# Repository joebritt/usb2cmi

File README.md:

# usb2cmi
USB Keyboard &amp; Mouse interface for the Fairlight CMI

More info can be found here:

https://docs.google.com/document/d/1SBbrsyc7bVfPzIFhJmcOLwGjMr6u-KO0Lp5tNpQLhYE/edit?usp=sharing

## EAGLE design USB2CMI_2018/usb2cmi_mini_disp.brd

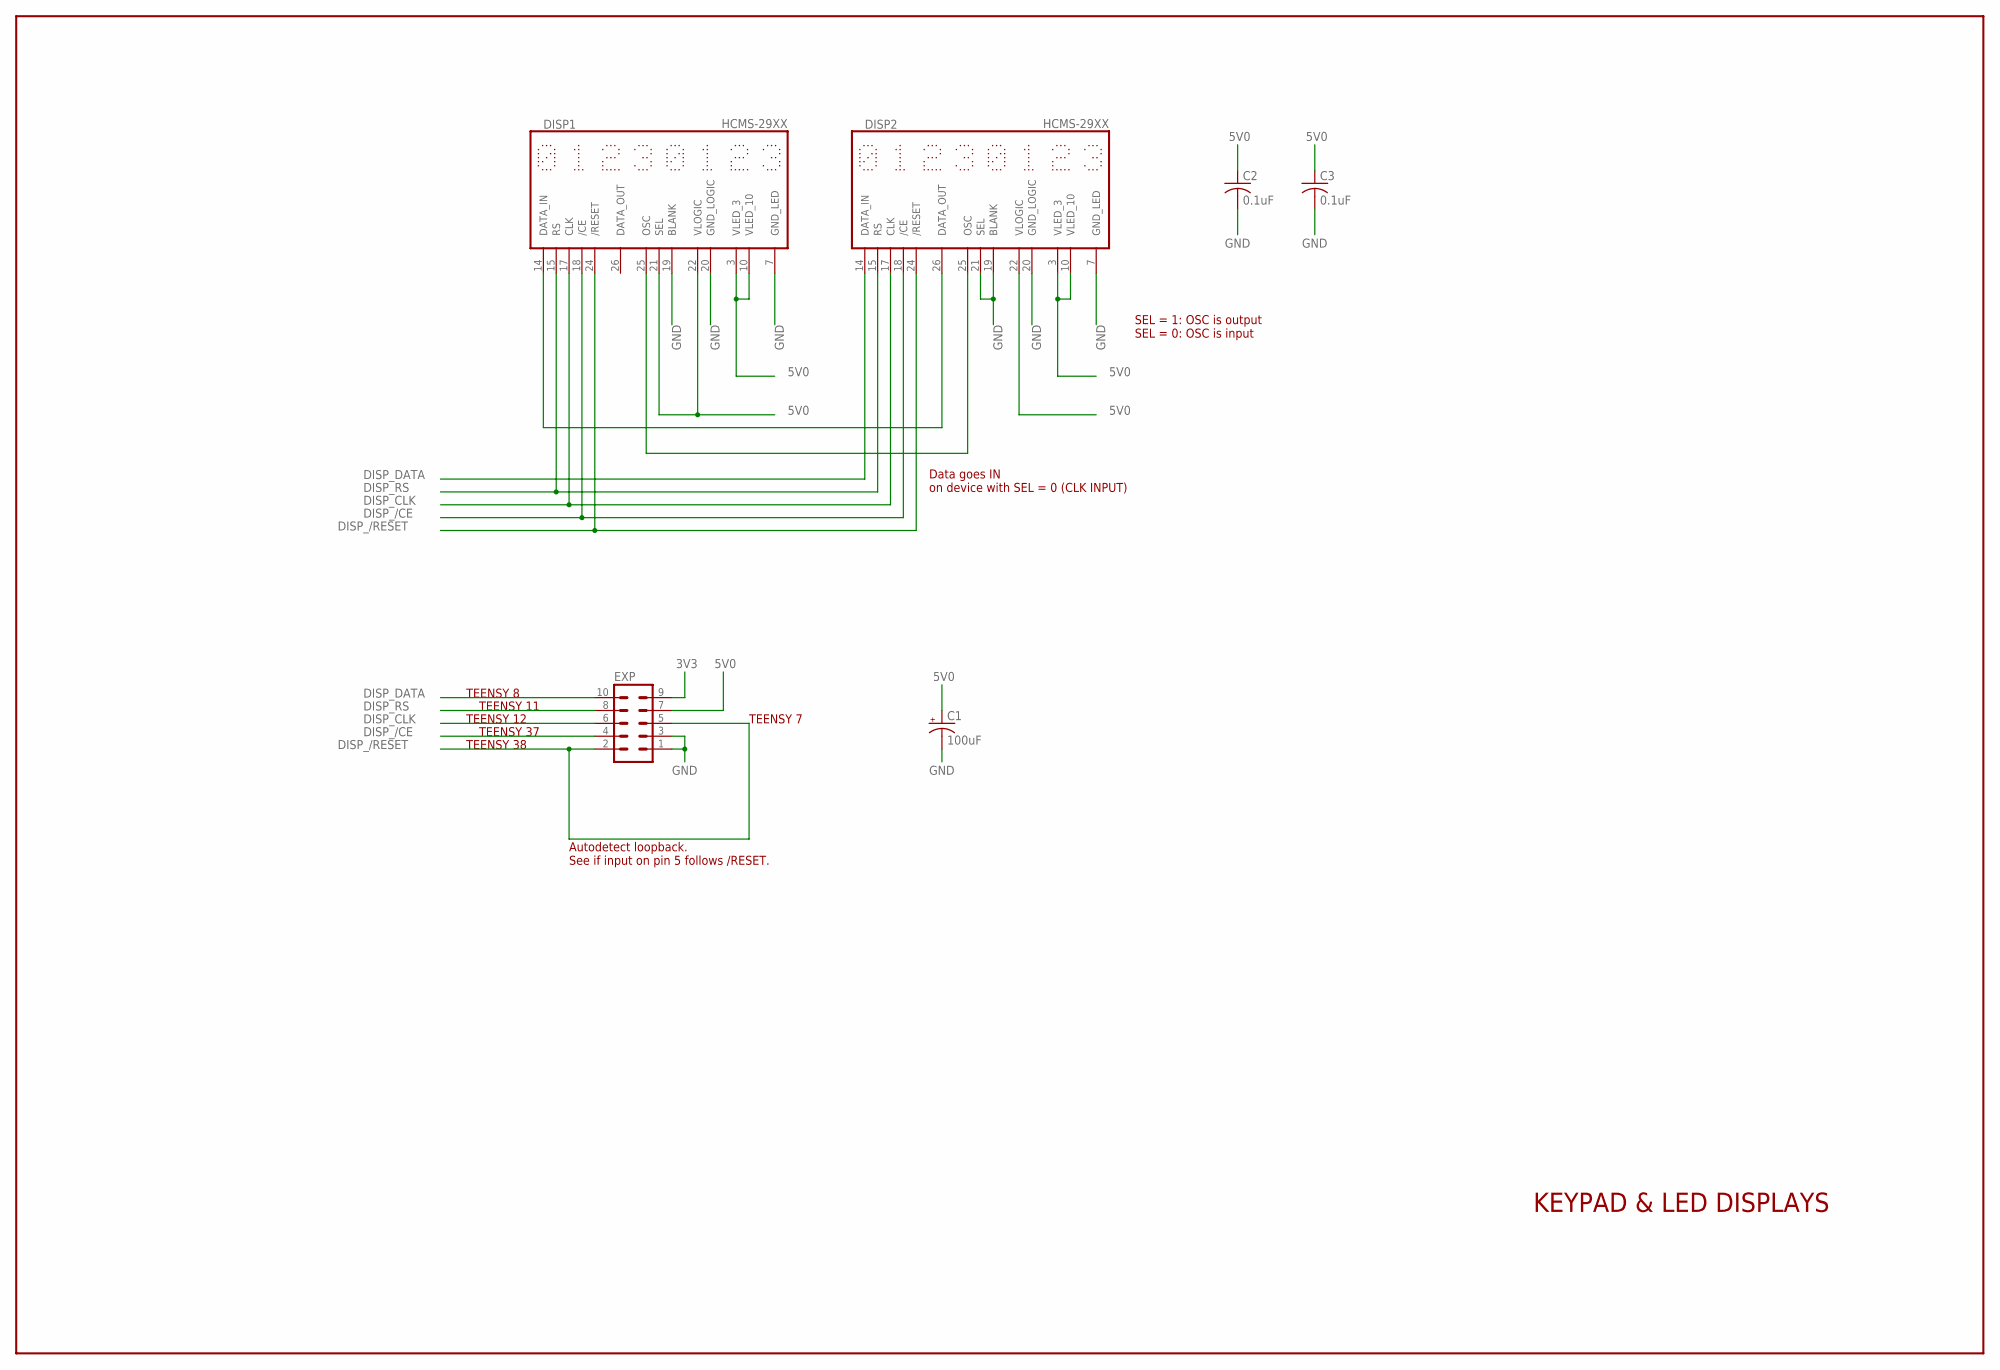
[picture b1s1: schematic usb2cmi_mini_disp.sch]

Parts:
C1: 100uF; E2,5-7
C2, C3: 0.1uF; C050-025X075
DISP1, DISP2: HCMS-29XX
EXP: MA05-2

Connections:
3V3: EXP.9
5V0: C1.+, C2.1, C3.1, DISP1.3 (VLED_3), DISP1.10 (VLED_10), DISP1.21 (SEL), DISP1.22 (VLOGIC), DISP2.3 (VLED_3), DISP2.10 (VLED_10), DISP2.22 (VLOGIC), EXP.7
DISP_/CE: DISP1.18 (/CE), DISP2.18 (/CE), EXP.4
DISP_/RESET: DISP1.24 (/RESET), DISP2.24 (/RESET), EXP.2, EXP.5
DISP_CLK: DISP1.17 (CLK), DISP2.17 (CLK), EXP.6
DISP_DATA: DISP2.14 (DATA_IN), EXP.10
DISP_RS: DISP1.15 (RS), DISP2.15 (RS), EXP.8
GND: C1.-, C2.2, C3.2, DISP1.7 (GND_LED), DISP1.19 (BLANK), DISP1.20 (GND_LOGIC), DISP2.7 (GND_LED), DISP2.19 (BLANK), DISP2.20 (GND_LOGIC), DISP2.21 (SEL), EXP.1, EXP.3
unnamed: DISP1.14 (DATA_IN), DISP2.26 (DATA_OUT)
unnamed: DISP1.25 (OSC), DISP2.25 (OSC)

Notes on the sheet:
KEYPAD & LED DISPLAYS
SEL = 1: OSC is output SEL = 0: OSC is input
Autodetect loopback. See if input on pin 5 follows /RESET.
Data goes IN on device with SEL = 0 (CLK INPUT)
TEENSY 7
TEENSY 38
TEENSY 37
TEENSY 12
TEENSY 11
TEENSY 8

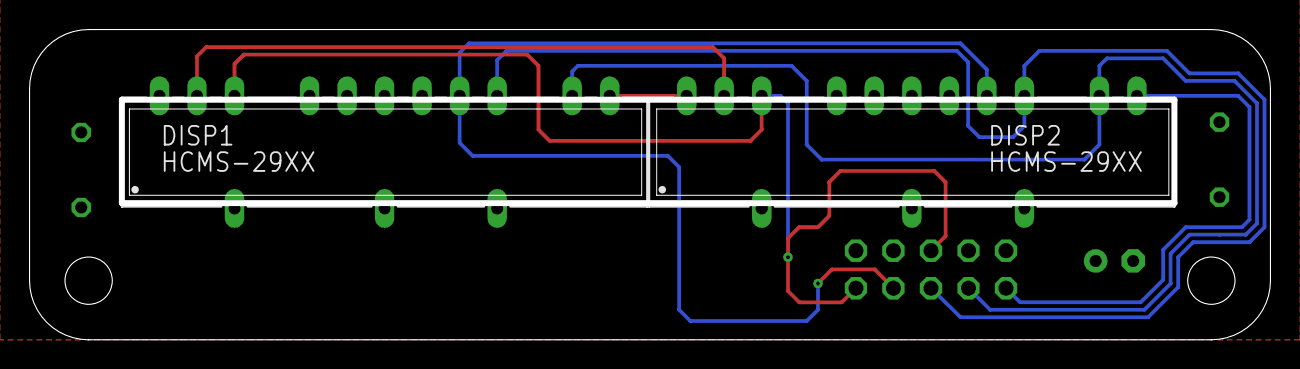
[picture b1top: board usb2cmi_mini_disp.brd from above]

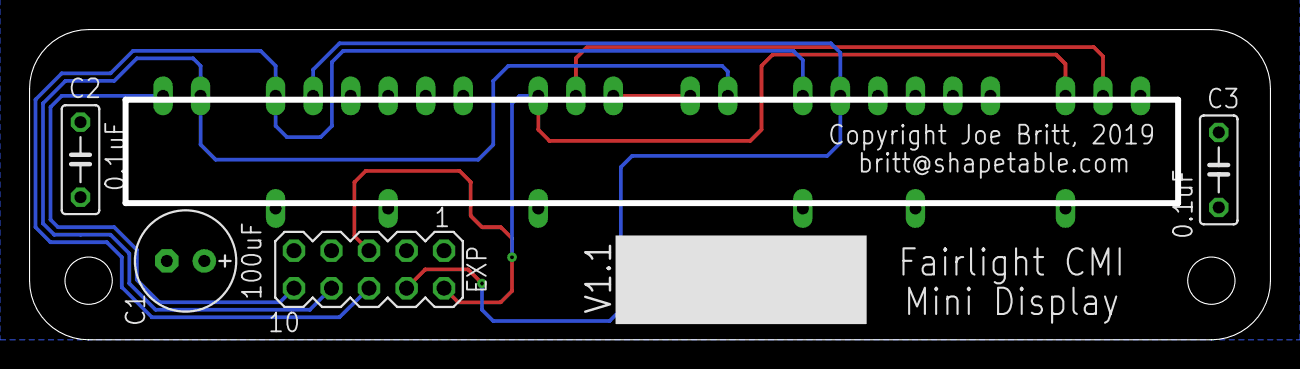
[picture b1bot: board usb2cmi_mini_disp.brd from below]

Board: 2 copper layers, 84.0 x 21.0 mm, 6 parts (4 on the bottom side), 9 nets.

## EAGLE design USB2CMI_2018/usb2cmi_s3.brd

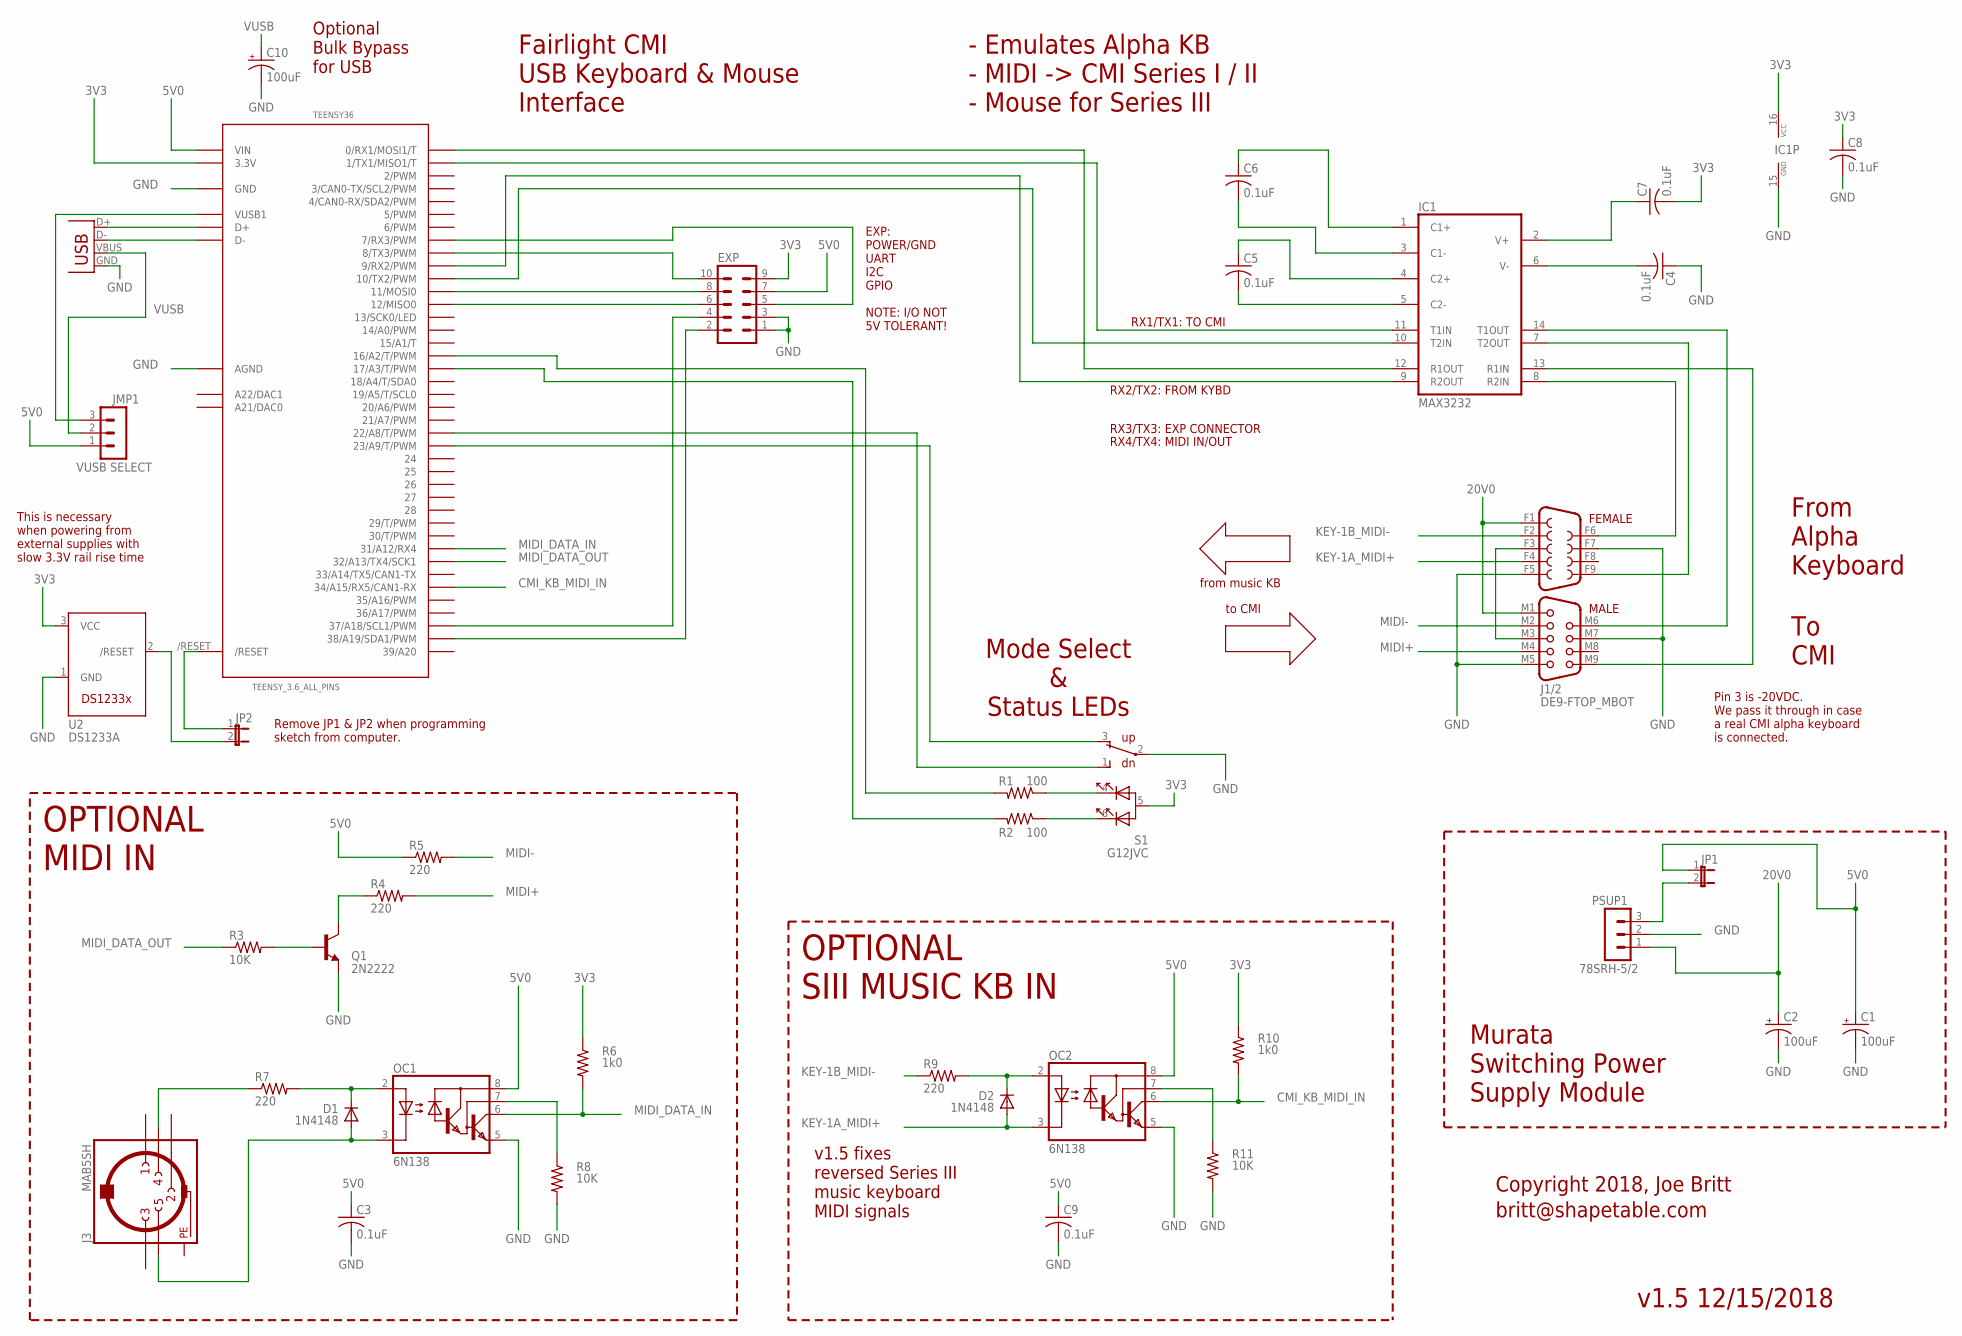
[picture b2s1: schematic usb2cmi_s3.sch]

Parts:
C1, C10: 100uF; E2,5-7
C2: 100uF; E3,5-10
C3, C4, C5, C6, C7, C8, C9: 0.1uF; C050-025X075
D1, D2: 1N4148; DO35-7
EXP: MA05-2
IC1: MAX3232; DIL16
J1/2: DE9-FTOP_MBOT; DE9_FTOP_MBOT
J3: MAB5SH
J4: USB-A-H
JMP1: VUSB SELECT; MA03-1
JP1, JP2: JP1E; JP1
OC1, OC2: 6N138; DIL08-NARROW
PSUP1: 78SRH-5/2; MA03-1
Q1: 2N2222; TO92-EBC-OVAL
R1, R2: 100; 0207/10
R3, R8, R11: 10K; 0207/10
R4, R5, R7, R9: 220; 0207/10
R6, R10: 1k0; 0207/10
S1: G12JVC
TEENSY36: TEENSY_3.6_ALL_PINS
U2: DS1233A; TO-92-

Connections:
3V3: C7.2, C8.1, EXP.9, IC1.16 (VCC), R6.1, R10.1, S1.5 (A), TEENSY36.3.3V, TEENSY36.3.3V3 (3.3V), U2.3 (VCC)
5V0: C1.+, C3.1, C9.1, EXP.7, JMP1.1, JP1.1, OC1.8 (VCC), OC2.8 (VCC), R5.1, TEENSY36.VIN
20V0: C2.+, J1/2.F1, J1/2.M1, PSUP1.1
CMI_KB_MIDI_IN: OC2.6 (VO), R10.2, TEENSY36.34/A15 (34/A15/RX5/CAN1-RX)
GND: C1.-, C2.-, C3.2, C4.1, C8.2, C9.2, C10.-, EXP.1, EXP.3, IC1.15 (GND), J1/2.F5, J1/2.F7, J1/2.M5, J1/2.M7, J4.GND, OC1.5 (GND), OC2.5 (GND), PSUP1.2, Q1.E, R8.2, R11.2, S1.2 (COM), TEENSY36.AGND, TEENSY36.GND, TEENSY36.GND1 (GND), TEENSY36.GND3 (GND), TEENSY36.GND4 (GND), U2.1 (GND)
KEY-1A_MIDI+: D2.A, J1/2.F4, OC2.3 (C)
KEY-1B_MIDI-: J1/2.F2, R9.1
MIDI+: J1/2.M4, R4.2
MIDI-: J1/2.M2, R5.2
MIDI_DATA_IN: OC1.6 (VO), R6.2, TEENSY36.31/A12 (31/A12/RX4)
MIDI_DATA_OUT: R3.1, TEENSY36.32/A13 (32/A13/TX4/SCK1)
unnamed: JP2.1, TEENSY36./RESET
unnamed: JP2.2, U2.2 (/RESET)
unnamed: EXP.5, TEENSY36.7 (7/RX3/PWM)
unnamed: EXP.10, TEENSY36.8 (8/TX3/PWM)
unnamed: EXP.8, TEENSY36.11 (11/MOSI0)
unnamed: EXP.6, TEENSY36.12 (12/MISO0)
unnamed: IC1.9 (R2OUT), TEENSY36.9 (9/RX2/PWM)
unnamed: R1.1, S1.4 (K_RED)
unnamed: R2.1, S1.6 (K_GRN)
unnamed: R2.2, TEENSY36.17/A3 (17/A3/T/PWM)
unnamed: R1.2, TEENSY36.16/A2 (16/A2/T/PWM)
unnamed: S1.1 (DOWN), TEENSY36.22/A8 (22/A8/T/PWM)
unnamed: S1.3 (UP), TEENSY36.23/A9 (23/A9/T/PWM)
unnamed: J4.D+, TEENSY36.D+
unnamed: J4.D-, TEENSY36.D-
unnamed: JMP1.3, TEENSY36.VUSB1
unnamed: C5.2, IC1.5 (C2-)
unnamed: C5.1, IC1.4 (C2+)
unnamed: C6.2, IC1.3 (C1-)
unnamed: C6.1, IC1.1 (C1+)
unnamed: C4.2, IC1.6 (V-)
unnamed: IC1.11 (T1IN), TEENSY36.1 (1/TX1/MISO1/T)
unnamed: Q1.B, R3.2
unnamed: IC1.14 (T1OUT), J1/2.M6
unnamed: C7.1, IC1.2 (V+)
unnamed: D1.C, OC1.2 (A), R7.2
unnamed: D1.A, J3.5, OC1.3 (C)
unnamed: Q1.C, R4.1
unnamed: J3.4, R7.1
unnamed: IC1.13 (R1IN), J1/2.M9
unnamed: IC1.12 (R1OUT), TEENSY36.0 (0/RX1/MOSI1/T)
unnamed: IC1.10 (T2IN), TEENSY36.10 (10/TX2/PWM)
unnamed: IC1.8 (R2IN), J1/2.F6
unnamed: IC1.7 (T2OUT), J1/2.F9
unnamed: J1/2.F3, J1/2.M3
unnamed: OC1.7 (VB), R8.1
unnamed: JP1.2, PSUP1.3
unnamed: D2.C, OC2.2 (A), R9.2
unnamed: OC2.7 (VB), R11.1
PE: J3.PE, J3.PE@ (PE)
SCL1: EXP.4, TEENSY36.37/A18 (37/A18/SCL1/PWM)
SDA1: EXP.2, TEENSY36.38/A19 (38/A19/SDA1/PWM)
VUSB: C10.+, J4.VBUS, JMP1.2

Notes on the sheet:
OPTIONAL MIDI IN
Murata Switching Power Supply Module
From Alpha Keyboard
To CMI
RX1/TX1: TO CMI
RX2/TX2: FROM KYBD
RX3/TX3: EXP CONNECTOR
RX4/TX4: MIDI IN/OUT
EXP: POWER/GND UART I2C GPIO NOTE: I/O NOT 5V TOLERANT!
Mode Select & Status LEDs
Pin 3 is -20VDC. We pass it through in case a real CMI alpha keyboard is connected.
Copyright 2018, Joe Britt
britt@shapetable.com
Fairlight CMI USB Keyboard & Mouse Interface
- Emulates Alpha KB - MIDI -> CMI Series I / II - Mouse for Series III
This is necessary when powering from external supplies with slow 3.3V rail rise time
Remove JP1 & JP2 when programming sketch from computer.
from music KB
to CMI
OPTIONAL SIII MUSIC KB IN
Optional Bulk Bypass for USB
v1.5 fixes reversed Series III music keyboard MIDI signals
v1.5 12/15/2018

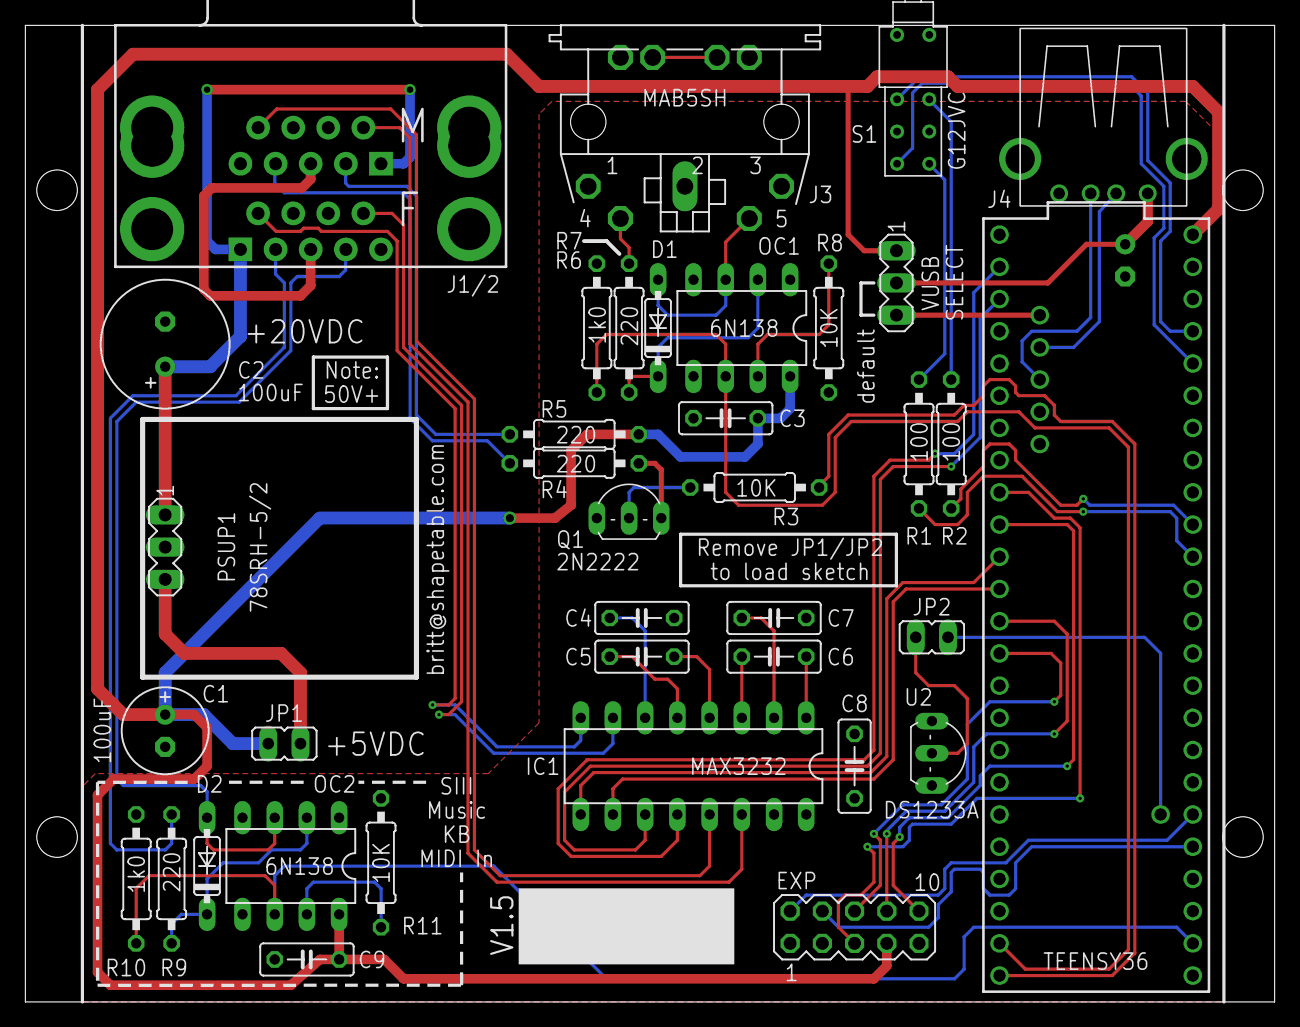
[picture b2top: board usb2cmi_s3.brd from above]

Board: 2 copper layers, 98.5 x 77.0 mm, 38 parts (1 on the bottom side), 54 nets.

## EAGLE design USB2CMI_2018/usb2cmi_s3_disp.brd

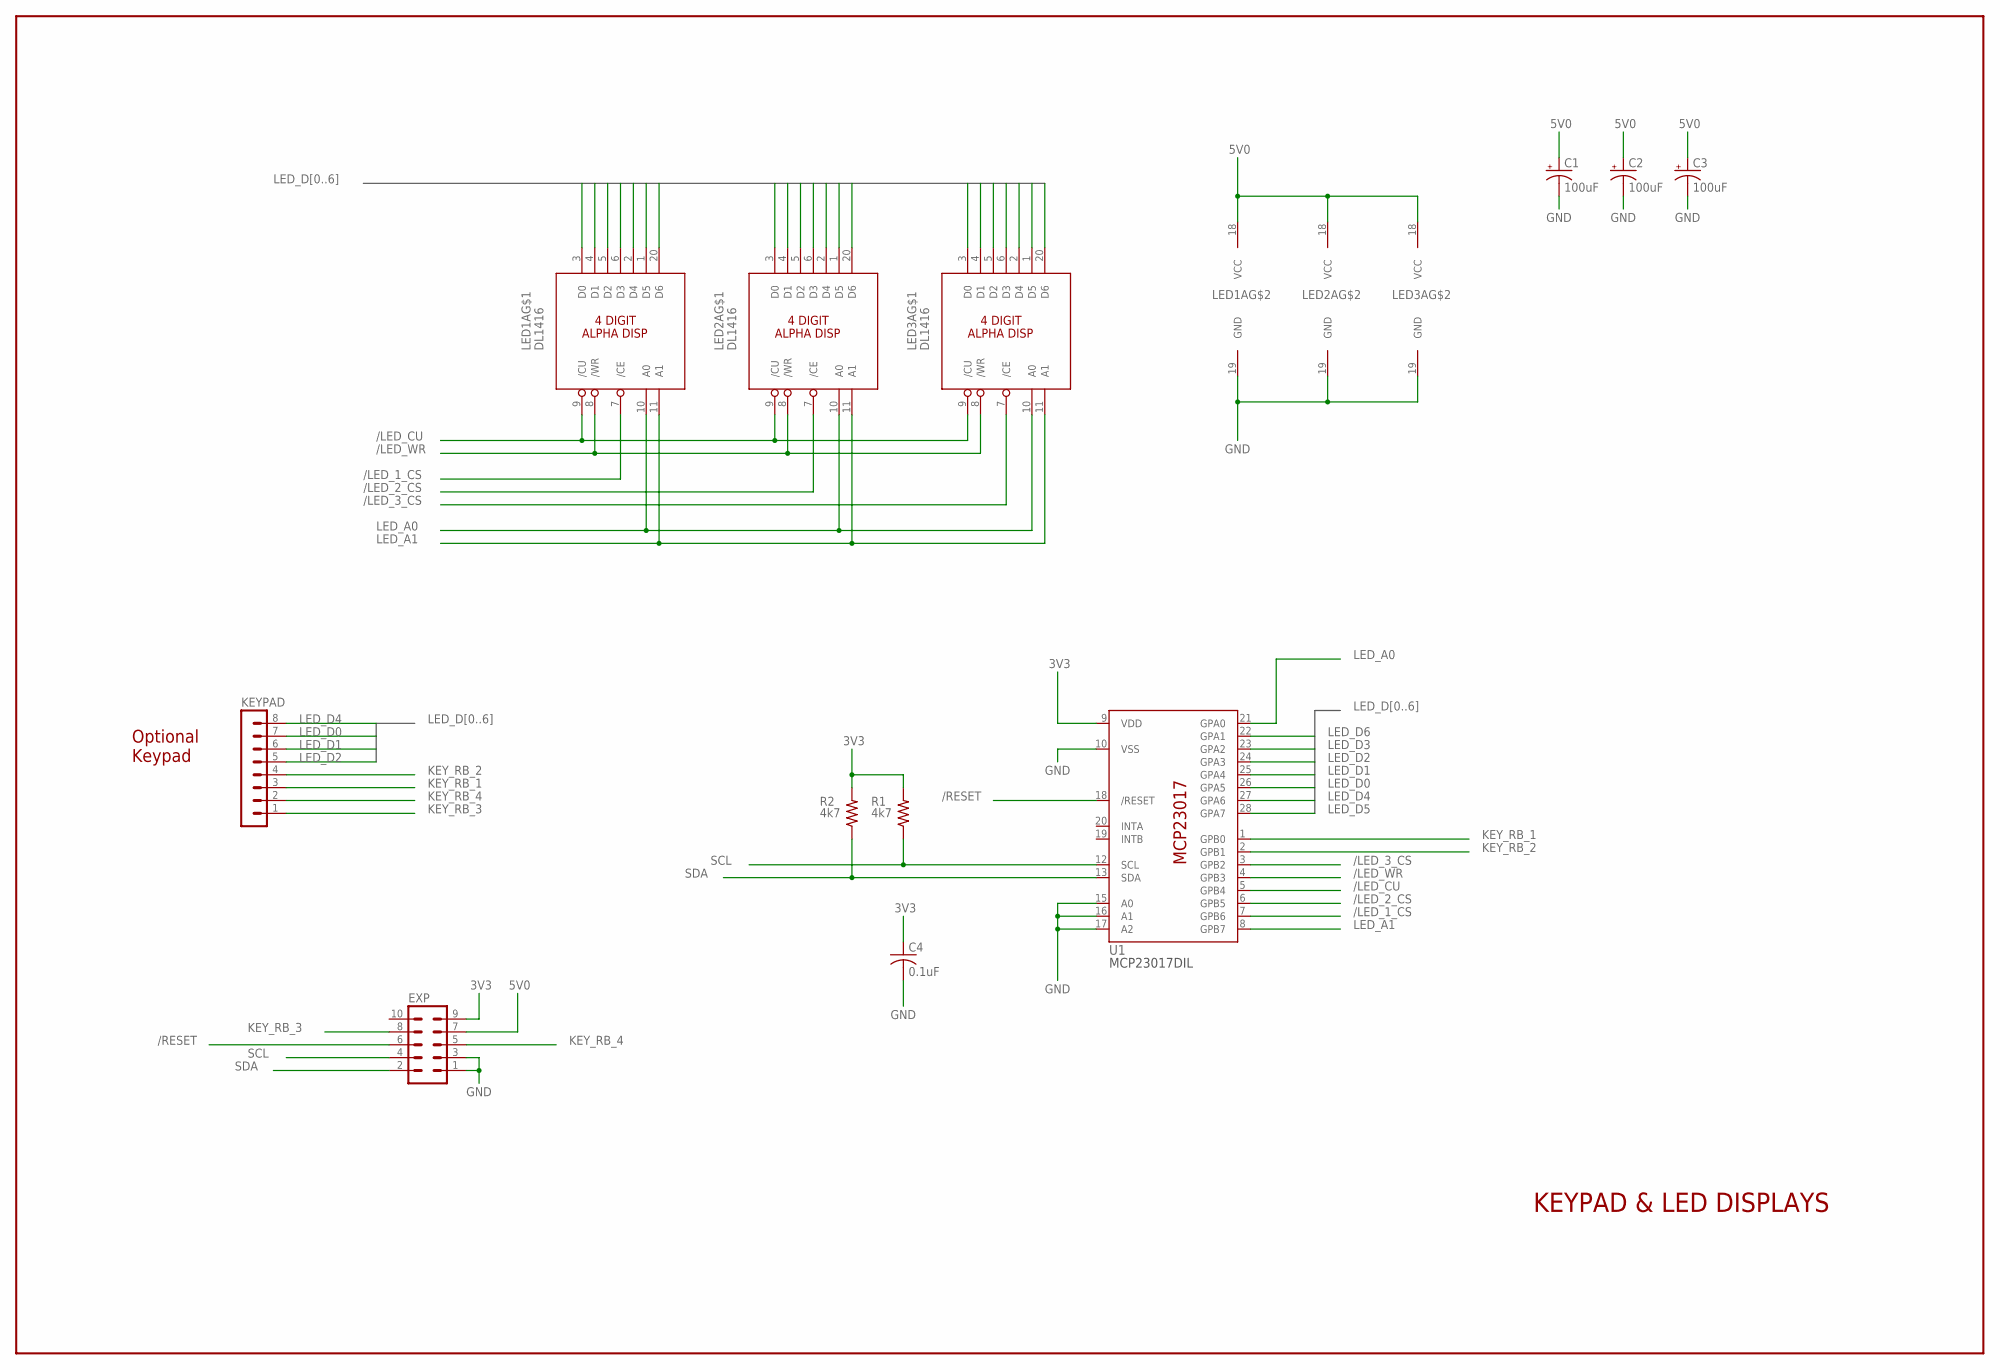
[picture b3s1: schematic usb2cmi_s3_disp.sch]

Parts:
C1, C2, C3: 100uF; E2,5-7
C4: 0.1uF; C050-025X075
EXP: MA05-2
KEYPAD: MA08-1
LED1A, LED2A, LED3A: DL1416; DIL20
R1, R2: 4k7; 0207/10
U1: MCP23017DIL; DIL28-3

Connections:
3V3: C4.1, EXP.9, R1.2, R2.2, U1.9 (VDD)
5V0: C1.+, C2.+, C3.+, EXP.7, LED1A.18 (VCC), LED2A.18 (VCC), LED3A.18 (VCC)
/LED_1_CS: LED1A.7 (/CE), U1.7 (GPB6)
/LED_2_CS: LED2A.7 (/CE), U1.6 (GPB5)
/LED_3_CS: LED3A.7 (/CE), U1.3 (GPB2)
/LED_CU: LED1A.9 (/CU), LED2A.9 (/CU), LED3A.9 (/CU), U1.5 (GPB4)
/LED_WR: LED1A.8 (/WR), LED2A.8 (/WR), LED3A.8 (/WR), U1.4 (GPB3)
/RESET: EXP.6, U1.18 (/RESET)
GND: C1.-, C2.-, C3.-, C4.2, EXP.1, EXP.3, LED1A.19 (GND), LED2A.19 (GND), LED3A.19 (GND), U1.10 (VSS), U1.15 (A0), U1.16 (A1), U1.17 (A2)
KEY_RB_1: KEYPAD.3, U1.1 (GPB0)
KEY_RB_2: KEYPAD.4, U1.2 (GPB1)
KEY_RB_3: EXP.8, KEYPAD.1
KEY_RB_4: EXP.5, KEYPAD.2
LED_A0: LED1A.10 (A0), LED2A.10 (A0), LED3A.10 (A0), U1.21 (GPA0)
LED_A1: LED1A.11 (A1), LED2A.11 (A1), LED3A.11 (A1), U1.8 (GPB7)
LED_D0: KEYPAD.7, LED1A.3 (D0), LED2A.3 (D0), LED3A.3 (D0), U1.26 (GPA5)
LED_D1: KEYPAD.6, LED1A.4 (D1), LED2A.4 (D1), LED3A.4 (D1), U1.25 (GPA4)
LED_D2: KEYPAD.5, LED1A.5 (D2), LED2A.5 (D2), LED3A.5 (D2), U1.24 (GPA3)
LED_D3: LED1A.6 (D3), LED2A.6 (D3), LED3A.6 (D3), U1.23 (GPA2)
LED_D4: KEYPAD.8, LED1A.2 (D4), LED2A.2 (D4), LED3A.2 (D4), U1.27 (GPA6)
LED_D5: LED1A.1 (D5), LED2A.1 (D5), LED3A.1 (D5), U1.28 (GPA7)
LED_D6: LED1A.20 (D6), LED2A.20 (D6), LED3A.20 (D6), U1.22 (GPA1)
SCL: EXP.4, R1.1, U1.12 (SCL)
SDA: EXP.2, R2.1, U1.13 (SDA)

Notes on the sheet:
KEYPAD & LED DISPLAYS
Optional Keypad

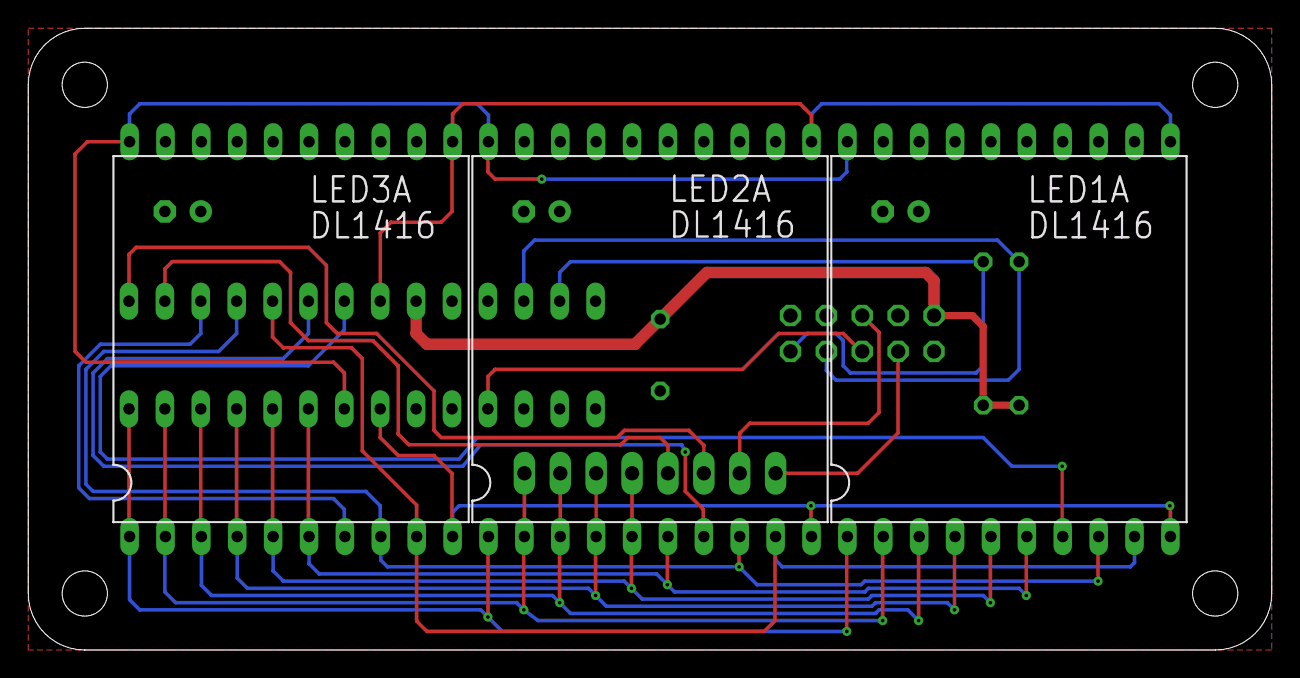
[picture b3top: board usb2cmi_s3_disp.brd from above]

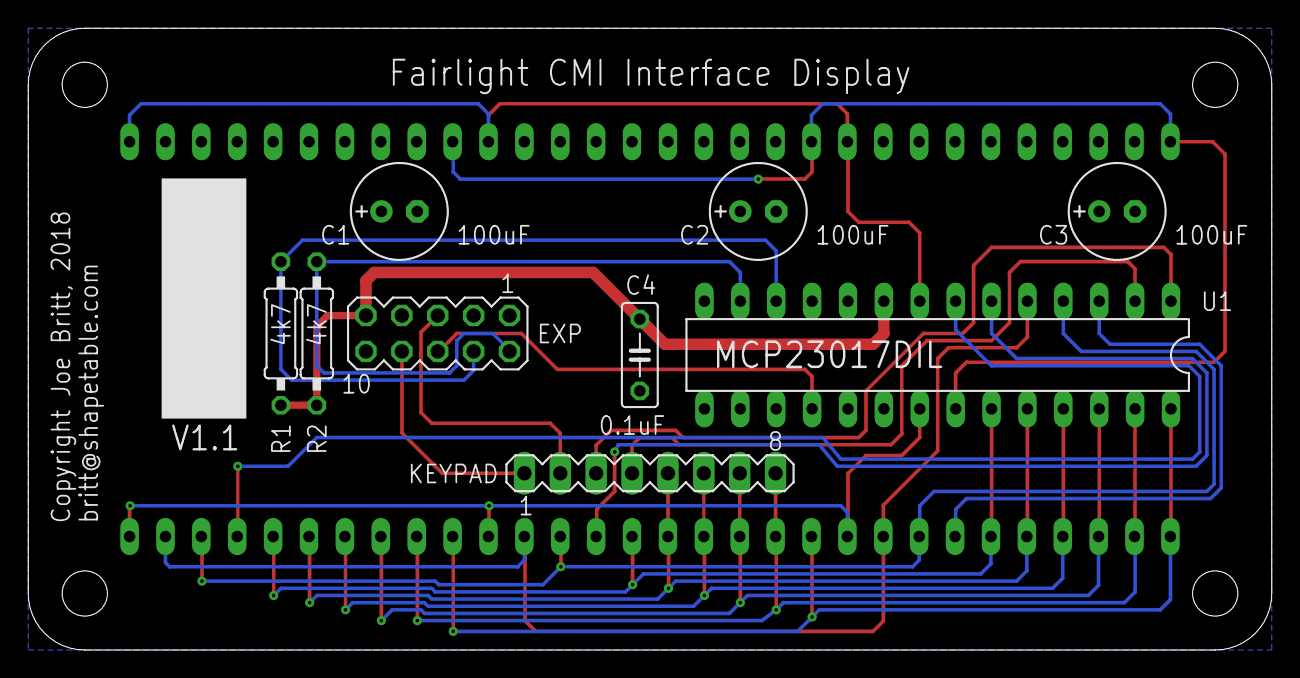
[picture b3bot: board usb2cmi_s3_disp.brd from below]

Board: 2 copper layers, 88.0 x 44.0 mm, 12 parts (9 on the bottom side), 24 nets.

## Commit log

2018-07-02 Add files via upload
    Initial commit.
2018-08-06 Updates for MIDI and LED display
2018-09-01 Add files via upload
    Eagle schematic & board design files for main board and display board.
    PDF versions of schematics.
    Front Panel Designer files for top & rear aluminum panels.
    PDF of front (display) panel, for laser cutting red plexiglass.
2018-09-01 Delete usb2cmi.ino
    uploading latest version in a directory
2018-09-01 Add files via upload
    USB2CMI interface Arduino Sketch
2018-09-01 Add files via upload
    Added delay to legacy music KB LED display write, was seeing digit 2 get the wrong val.
    Added support for MIDI control of Series I/II. Notes and Pitchbend (as Control 1 Slider) implemented.
2018-09-04 Add files via upload
    Keypad scanning and reporting added.
2018-09-04 Delete usb2cmi.ino
    accidentally checked into wrong place.
2018-09-04 Add files via upload
    Added support for keypad.
2018-09-04 Add files via upload
    Autodetect i2c port expander, which is used for the LED displays & keypad.
    If we don't find it at boot assume we don't have it installed, don't try to do any more i2c transactions.
2018-09-08 Add files via upload
    - MIDI Pitchbend -> CMI Control Slider 1
    - MIDI CC 75 - 79 -> CMI Control Sliders 2 - 6
    - MIDI CC 80 - 83 -> CMI Control Switches 1 - 4
    - MIDI CC 16 -> CMI Control Switch 5
    - Removed 1ms delay() when writing to legacy keyboard LED displays
2018-12-10 Add files via upload
    Updated schematic and board v1.4.
    Front Panel Designer file for basic version.
    The main change is addition of a second MIDI optoisolator. This lets the interface also receive MIDI data from a Series III music keyboard (if attached), so we can merge that music keyboard data with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
    (This was already supported for Series I/II, which don't use MIDI for their music keyboards.)
2018-12-10 Add files via upload
    The schematic file seemed to have gotten missed.
2018-12-10 Add files via upload
    Again
2018-12-10 Add files via upload
    Added support for MIDI in from Series III music keyboard on Serial5.
2018-12-10 Delete usb2cmi_s3.sch
    going to replace
2018-12-10 Add files via upload
    Design schematic, v1.4
2018-12-16 Add files via upload
    v1.5 of USB2CMI PCB.
    Fixes reversed MIDI +/- signals from legacy SIII keyboard.
    Adds optional 100uF bulk bypass cap across USB host power/ground.
2018-12-16 Add files via upload
    Verified SIII legacy music keyboard input works.
    Still need to do proper MIDI merge between SIII legacy MIDI keyboard and interface MIDI in.
    Blink version number (count red flashes) on toggle switch LED at boot.
2019-04-12 Mini display board.
    Eagle schematic & PCB design for the small HCMS display version.
2019-06-17 v1.3, Add support for HDSP21xx LED displays
    Box now supports HDSP21xx LED displays as well as classic DL1416 displays.
2019-06-17 Delete usb2cmi_13.ino
    uploaded test version by mistake.
2019-06-17 v13, Add support for HDSP21xx LED displays
2019-12-01 Fix bugs with Shift/Control modifier keys on SIII
    Shift and Control on the USB keyboard now have the proper behavior on SIII.
    Removed some debug code that had been left in.
    Fixed UART definitions, wrong mapping was accidentally checked in last time.
    Increased version to 1.4.
    More details:
    On a Series III system, holding down Shift or Control should change the icons displayed at the bottom of the CMI screen. These icons map onto the F1-F15 function keys, and so the function of a each k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
2019-12-02 Forgot to add checkin comment at top of file, added.
2019-12-02 oops
2019-12-02 Forgot to add comment & version update at top of file
2020-03-09 Add files via upload
    Fix problem that sometimes prevented mouse from being detected.
2020-03-09 Fixed problem with hub/keyboard/mouse detection
2021-07-18 v1.6, fix shift key bug, use F13/F14/F15 on Apple keyboards
    v1.6
    - Fixed Shift/Control behavior for arrow keys on Series III. Thanks to Cris Blyth and Andrei Kudryavtsev for finding that bug and letting me know about it!
    - Apple USB keyboards have F13, F14, and F15 keys. Map those to CMI F13, F14, and F15.

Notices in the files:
USB2CMI_2018/usb2cmi_mini_disp.brd:
Copyright Joe Britt, 2019
USB2CMI_2018/usb2cmi_s3_disp.brd:
Copyright Joe Britt, 2018
parts and their libraries:
SparkFun-Connectors: Licensing: Creative Commons ShareAlike 4.0 International - https://creativecommons.org/licenses/by-sa/4.0
